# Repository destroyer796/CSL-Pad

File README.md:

# CSL-Pad
A [Hackpad](https://hackpad.hackclub.com/) made for [Hack Club](https://hackclub.com/) designed to be used with a Fanatec CDL DD wheelbase

## BOM:
Provided by Hack Club as a part of the Hackpad project:
 - 16x Cherry MX switches
 - 1x EC11 Encoder
 - 1x PCB
 - 17x Through-hole 1N4148 Diodes
 - 16x WS2812B LEDs
 - 1x XIAO RP2040
 - 1x 3D Printed Case
 - 16x DSA Keycaps
 - 1x 3D Printed Knob
 - 7x M3x5x4 Heatset Inserts
   
 Self sourced:
 - [3x M3x6 SHCS Screws](https://www.amazon.com/BNUOK-120pcs-Stainless-Threads-Spanner/dp/B0DJQG5YLF/ref=sr_1_2_sspa?crid=CRACPU7L2KC4&dib=eyJ2IjoiMSJ9.IMCY_53JHXm5rNDAjyYVu7BtEWK2lbl6ZRTYLSm09dUkGYZqyqbg4onIhqBgKfWZQ-cHt_QhAD7pIcmXD0e7RkiCsK1L7ik_0HRclK3k9YAh37S-kDjcX-T6UeqX8aHC8XLt1hIWsWsg-wUtcOLQgJV2gB70HIx5jwNEVcQPXUe72bSh_2U9xKkuOQbDS-uHjQ2ftxnDxcZOeuSoQw53MJq6Ah_pCiqsAtpXxshg3zI.lzkIw-GMszdDmza4k0AX-ZfpVpUoSKq0ElLhG5Aq70c&dib_tag=se&keywords=m3x6%2Bscrews&qid=1751311357&sprefix=m3x6%2Bscrews%2Caps%2C96&sr=8-2-spons&sp_csd=d2lkZ2V0TmFtZT1zcF9hdGY&th=1)
 - [4x M3x12 SHCS Screws](https://www.amazon.com/BNUOK-120pcs-Stainless-Threads-Spanner/dp/B0DJQG5YLF/ref=sr_1_2_sspa?crid=CRACPU7L2KC4&dib=eyJ2IjoiMSJ9.IMCY_53JHXm5rNDAjyYVu7BtEWK2lbl6ZRTYLSm09dUkGYZqyqbg4onIhqBgKfWZQ-cHt_QhAD7pIcmXD0e7RkiCsK1L7ik_0HRclK3k9YAh37S-kDjcX-T6UeqX8aHC8XLt1hIWsWsg-wUtcOLQgJV2gB70HIx5jwNEVcQPXUe72bSh_2U9xKkuOQbDS-uHjQ2ftxnDxcZOeuSoQw53MJq6Ah_pCiqsAtpXxshg3zI.lzkIw-GMszdDmza4k0AX-ZfpVpUoSKq0ElLhG5Aq70c&dib_tag=se&keywords=m3x6%2Bscrews&qid=1751311357&sprefix=m3x6%2Bscrews%2Caps%2C96&sr=8-2-spons&sp_csd=d2lkZ2V0TmFtZT1zcF9hdGY&th=1)
 - [2x M6x16 SHCS Screws](https://www.amazon.com/Socket-Screws-Bolts-Grade-Threaded/dp/B0BHZTQTK4/ref=sr_1_8?crid=3FZ5JU8CND7SY&dib=eyJ2IjoiMSJ9._3nf3lRPS4-Z1h-GmcgYkykDGhvfTKGtKxUxMjFOxoZFWxgzl28p2iYhYbMx6paz_pvnqEk6o7NZBcpiGU3DyP_gW7RwZxptuaxUwtK26W26_L4cFaLHQYBj31hmVKNRbkiwN98w6wpI3y07jnP388ls9EM1c_5we-SRsVVq3GQvOFSpcqaqd2mWm2Z2fnXbIYk4RHREun1UH-R3yyvpmfJY3gaVss4WYirR8YvSfmM.stwOLhIi8EKcY4arjH6RI3oYIWyppEjICw92XBlwVKw&dib_tag=se&keywords=m6x16+screws&qid=1751311447&sprefix=m6x16+screws%2Caps%2C98&sr=8-8)

<video src="https://github.com/destroyer796/CSL-Pad/blob/main/media/CSL%20Pad%20v3.mp4" width="320" height="240" controls></video>

Project rendering

Exploded view

Schematic

PCB design

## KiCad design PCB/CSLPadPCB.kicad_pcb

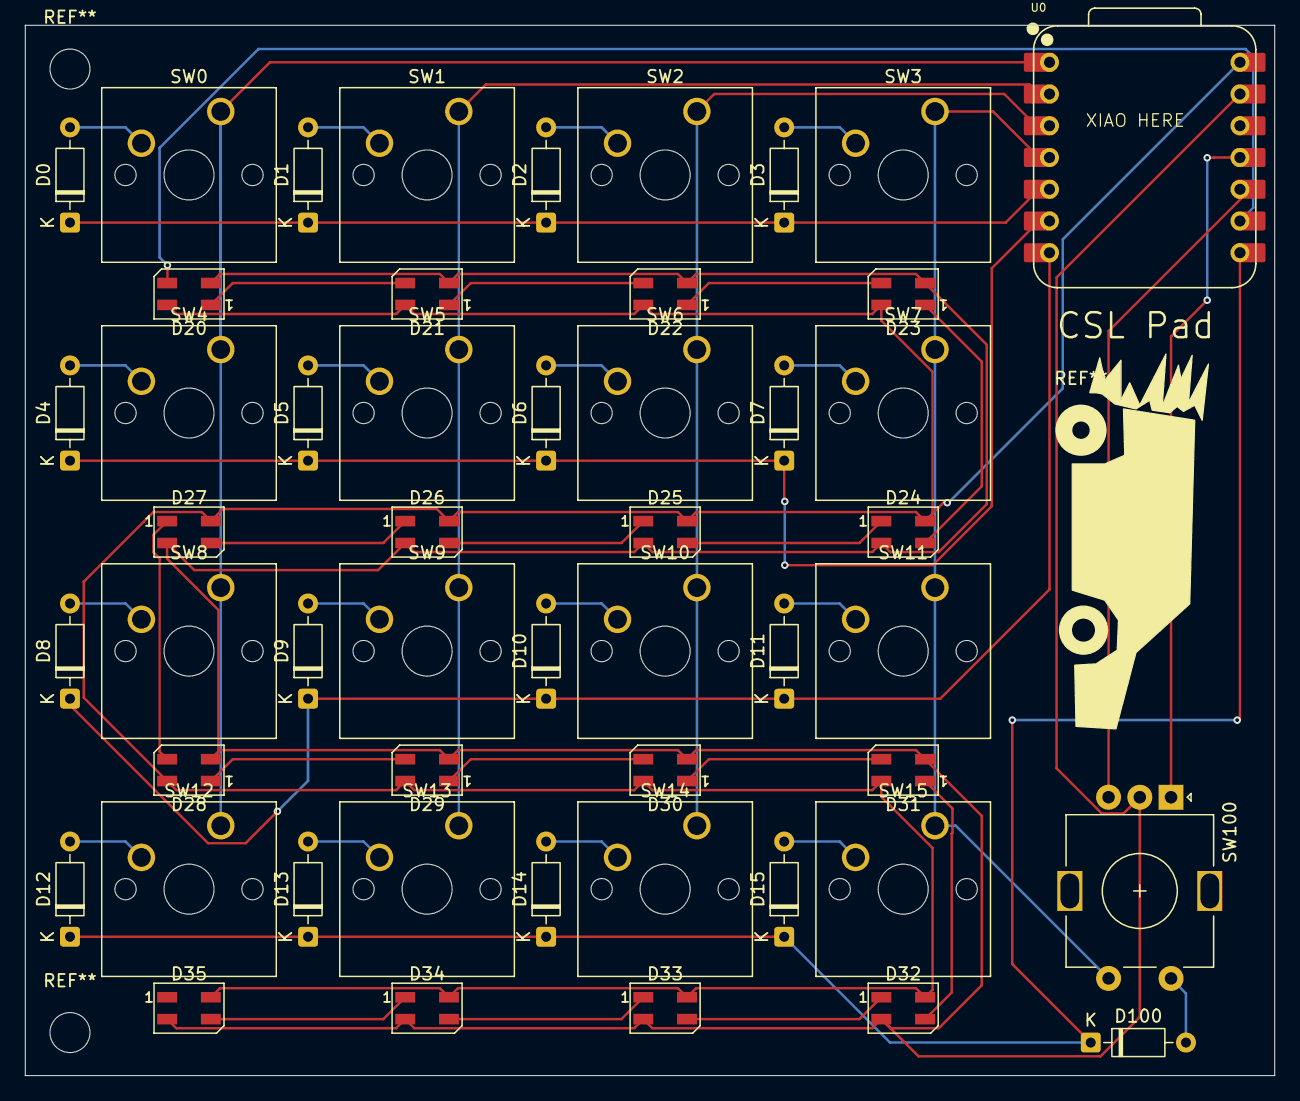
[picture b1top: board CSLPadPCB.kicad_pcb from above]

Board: 2 copper layers, 100.0 x 84.0 mm, 51 parts (0 on the bottom side), 45 nets.

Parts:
D0, D1, D2, D3, D4, D5, D6, D7, D8, D9, D10, D11, D12, D13, D14, D15, D100: 1N4148; D_DO-35_SOD27_P7.62mm_Horizontal
D20, D21, D22, D23, D24, D25, D26, D27, D28, D29, D30, D31, D32, D33, D34, D35: SK6812MINI; LED_SK6812MINI_PLCC4_3.5x3.5mm_P1.75mm
SW0, SW1, SW2, SW3, SW4, SW5, SW6, SW7, SW8, SW9, SW10, SW11, SW12, SW13, SW14, SW15: SW_Push; SW_Cherry_MX_1.00u_PCB
SW100: RotaryEncoder_Switch; RotaryEncoder_Alps_EC11E-Switch_Vertical_H20mm
U0: XIAO-RP2040-DIP

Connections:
+5V: D20.4 (VDD), D21.4 (VDD), D22.4 (VDD), D23.4 (VDD), D24.4 (VDD), D25.4 (VDD), D26.4 (VDD), D27.4 (VDD), D28.4 (VDD), D29.4 (VDD), D30.4 (VDD), D31.4 (VDD), D32.4 (VDD), D33.4 (VDD), D34.4 (VDD), D35.4 (VDD), U0.14 (VBUS)
COL0: SW0.1, SW4.1, SW8.1, SW12.1, U0.1 (GPIO26/ADC0/A0)
COL1: SW1.1, SW5.1, SW9.1, SW13.1, U0.2 (GPIO27/ADC1/A1)
COL2: SW2.1, SW6.1, SW10.1, SW14.1, U0.3 (GPIO28/ADC2/A2)
COL3: SW3.1, SW7.1, SW11.1, SW15.1, SW100.S1, U0.4 (GPIO29/ADC3/A3)
EC11A: SW100.A, U0.11 (GPIO3/MOSI)
EC11B: SW100.B, U0.10 (GPIO4/MISO)
EC11S2: D100.2 (A), SW100.S2
GND: D20.2 (VSS), D21.2 (VSS), D22.2 (VSS), D23.2 (VSS), D24.2 (VSS), D25.2 (VSS), D26.2 (VSS), D27.2 (VSS), D28.2 (VSS), D29.2 (VSS), D30.2 (VSS), D31.2 (VSS), D32.2 (VSS), D33.2 (VSS), D34.2 (VSS), D35.2 (VSS), SW100.C, U0.13 (GND)
LED: D20.3 (DIN), U0.9 (GPIO2/SCK)
unnamed: D0.2 (A), SW0.2
unnamed: D1.2 (A), SW1.2
unnamed: D2.2 (A), SW2.2
unnamed: D3.2 (A), SW3.2
unnamed: D4.2 (A), SW4.2
unnamed: D5.2 (A), SW5.2
unnamed: D6.2 (A), SW6.2
unnamed: D7.2 (A), SW7.2
unnamed: D8.2 (A), SW8.2
unnamed: D9.2 (A), SW9.2
unnamed: D10.2 (A), SW10.2
unnamed: D11.2 (A), SW11.2
unnamed: D12.2 (A), SW12.2
unnamed: D13.2 (A), SW13.2
unnamed: D14.2 (A), SW14.2
unnamed: D15.2 (A), SW15.2
unnamed: D20.1 (DOUT), D21.3 (DIN)
unnamed: D21.1 (DOUT), D22.3 (DIN)
unnamed: D22.1 (DOUT), D23.3 (DIN)
unnamed: D23.1 (DOUT), D24.3 (DIN)
unnamed: D24.1 (DOUT), D25.3 (DIN)
unnamed: D25.1 (DOUT), D26.3 (DIN)
unnamed: D26.1 (DOUT), D27.3 (DIN)
unnamed: D27.1 (DOUT), D28.3 (DIN)
unnamed: D28.1 (DOUT), D29.3 (DIN)
unnamed: D29.1 (DOUT), D30.3 (DIN)
unnamed: D30.1 (DOUT), D31.3 (DIN)
unnamed: D31.1 (DOUT), D32.3 (DIN)
unnamed: D32.1 (DOUT), D33.3 (DIN)
unnamed: D33.1 (DOUT), D34.3 (DIN)
unnamed: D34.1 (DOUT), D35.3 (DIN)
ROW0: D0.1 (K), D1.1 (K), D2.1 (K), D3.1 (K), U0.5 (GPIO6/SDA)
ROW1: D4.1 (K), D5.1 (K), D6.1 (K), D7.1 (K), U0.6 (GPIO7/SCL)
ROW2: D8.1 (K), D9.1 (K), D10.1 (K), D11.1 (K), U0.7 (GPIO0/TX)
ROW3: D12.1 (K), D13.1 (K), D14.1 (K), D15.1 (K), D100.1 (K), U0.8 (GPIO1/RX)

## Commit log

2025-06-30 Create example
2025-07-30 Create LICENSE
